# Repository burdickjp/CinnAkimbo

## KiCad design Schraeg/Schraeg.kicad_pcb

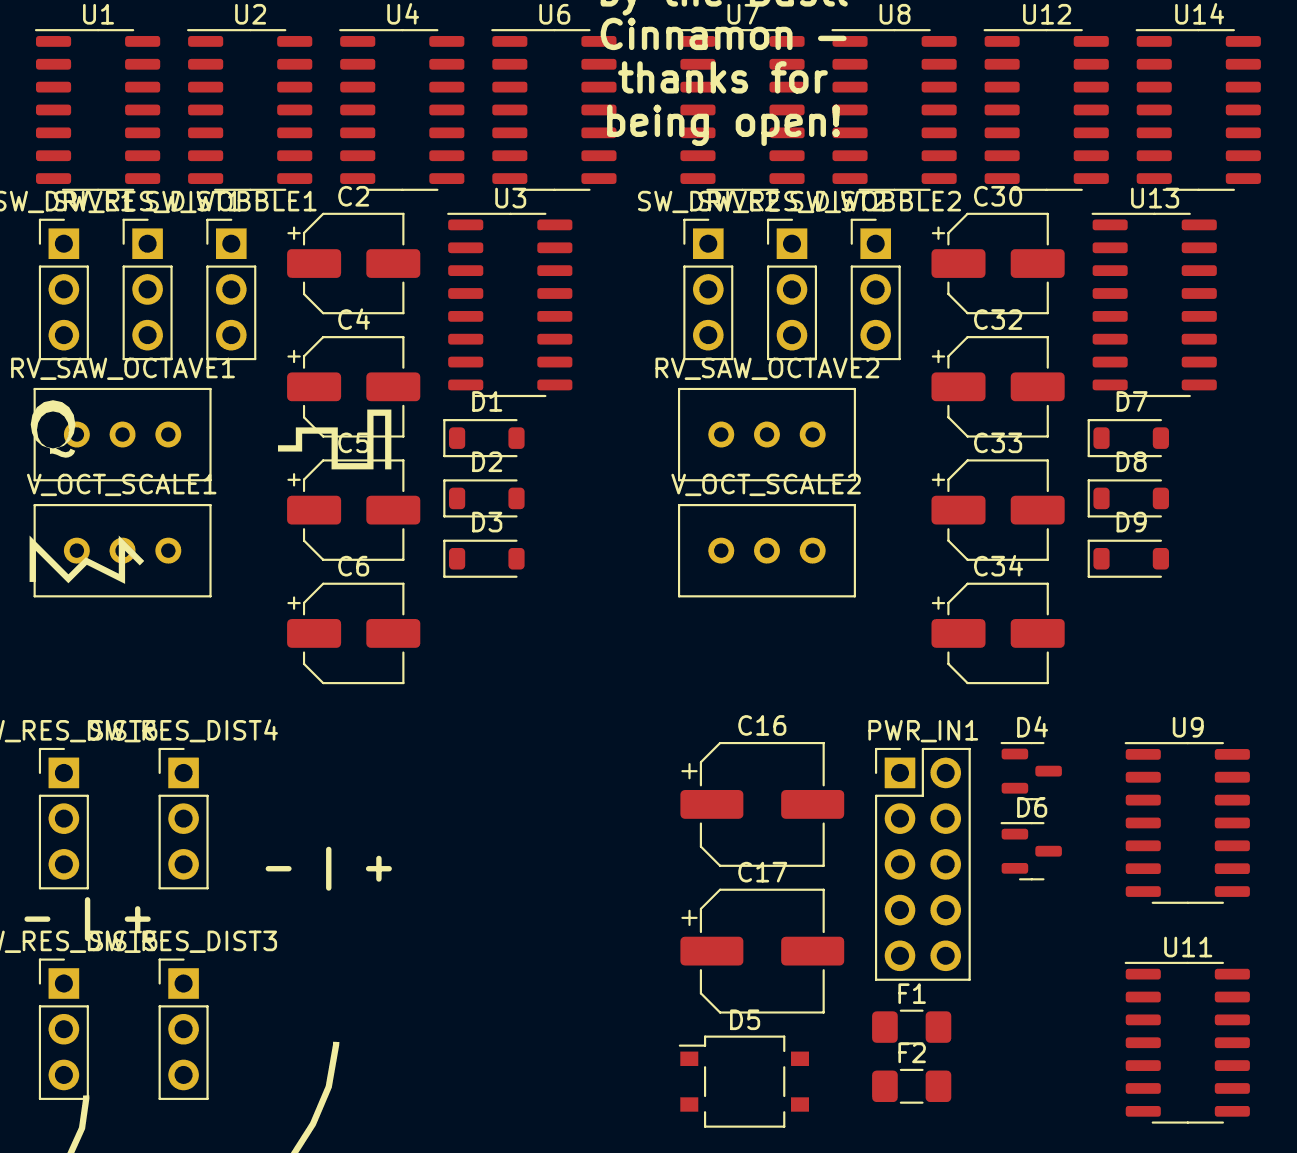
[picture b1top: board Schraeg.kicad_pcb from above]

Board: 2 copper layers, 49 parts (0 on the bottom side), 31 nets, no tracks yet.

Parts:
C2, C4, C5, C6, C30, C32, C33, C34: 10uF; CP_Elec_5x4.5
C16, C17: 22uF; CP_Elec_6.3x5.4
D1, D2, D7, D8: D_Small; D_SOD-123
D3, D9: 5V; D_SOD-123
D4, D6: LM4040DBZ-5; SOT-23
D5: MB2S; TO-269AA
F1, F2: Polyfuse; Fuse_1206_3216Metric_Pad1.42x1.75mm_HandSolder
PWR_IN1: EURO_PWR_2x5; PinHeader_2x05_P2.54mm_Vertical
RV_SAW_OCTAVE1, RV_SAW_OCTAVE2: 100k; Potentiometer_Bourns_3296W_Vertical
SW_DRIVE1, SW_DRIVE2: SW_SPDT; PinHeader_1x03_P2.54mm_Vertical
SW_RES_DIST1, SW_RES_DIST2, SW_RES_DIST3, SW_RES_DIST4, SW_RES_DIST5, SW_RES_DIST6: SW_SPDT; PinHeader_1x03_P2.54mm_Vertical
SW_WOBBLE1, SW_WOBBLE2: SW_SPDT; PinHeader_1x03_P2.54mm_Vertical
U1, U2, U4, U6, U7, U8, U9, U11, U12, U14: TL074; SOIC-14_3.9x8.7mm_P1.27mm
U3, U13: V2164; SOIC-16_3.9x9.9mm_P1.27mm
V_OCT_SCALE1, V_OCT_SCALE2: 5K; Potentiometer_Bourns_3296W_Vertical
svg2mod: G***; Schraeg Panel Graphics Inkscape

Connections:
+12V: C16.1, D5.3 (+), U1.4 (V+), U2.4 (V+), U3.16 (V+), U4.4 (V+), U6.4 (V+), U7.4 (V+), U8.4 (V+), U12.4 (V+), U13.16 (V+), U14.4 (V+)
-12V: C17.2, D5.4 (-), U1.11 (V-), U2.11 (V-), U3.9 (-V), U4.11 (V-), U6.11 (V-), U7.11 (V-), U8.11 (V-), U12.11 (V-), U13.9 (-V), U14.11 (V-)
/Invert Switch A/CV_OUT: SW_RES_DIST3.2 (B), U2.6 (-)
/Invert Switch D/CV_OUT: SW_RES_DIST6.2 (B), U12.6 (-)
/Left Channel/FM_CV_IN: D1.2 (A), U1.9 (-)
/Left Channel/FREQ_CV: D2.1 (K), V_OCT_SCALE1.2, V_OCT_SCALE1.3
/Left Channel/RES_CV: U3.3, U4.1
/Left Channel/RES_MOD: SW_RES_DIST1.3 (C), SW_WOBBLE1.3 (C)
/Right Channel/FM_CV_IN: D7.2 (A), U7.9 (-)
/Right Channel/FREQ_CV: D8.1 (K), V_OCT_SCALE2.2, V_OCT_SCALE2.3
/Right Channel/RES_CV: U13.3, U14.1
/Right Channel/RES_MOD: SW_RES_DIST2.3 (C), SW_WOBBLE2.3 (C)
GND: C16.2, C17.1, D4.2 (A), D6.1 (K), PWR_IN1.3 (GND), PWR_IN1.4 (GND), PWR_IN1.5 (GND), PWR_IN1.6 (GND), PWR_IN1.7 (GND), PWR_IN1.8 (GND), RV_SAW_OCTAVE1.3, RV_SAW_OCTAVE2.3, U1.5 (+), U1.10 (+), U1.12 (+), U2.5 (+), U2.10 (+), U3.8 (GND), U4.3 (+), U4.5 (+), U6.5 (+), U7.5 (+), U7.10 (+), U7.12 (+), U8.5 (+), U9.5 (+), U11.5 (+), U12.5 (+), U12.10 (+), U13.8 (GND), U14.3 (+)
unnamed: D1.1 (K), D2.2 (A), U1.8
unnamed: D3.2 (A), SW_RES_DIST1.2 (B)
unnamed: D5.1, F2.1
unnamed: D5.2, F1.1
unnamed: D7.1 (K), D8.2 (A), U7.8
unnamed: D9.2 (A), SW_RES_DIST2.2 (B)
unnamed: F1.2, PWR_IN1.1 (+12V), PWR_IN1.2 (+12V)
unnamed: F2.2, PWR_IN1.9 (-12V), PWR_IN1.10 (-12V)
unnamed: SW_DRIVE1.2 (B), U1.14
unnamed: SW_DRIVE2.2 (B), U7.14
unnamed: SW_RES_DIST3.1 (A), U4.7
unnamed: SW_RES_DIST4.1 (A), U6.7
unnamed: SW_RES_DIST5.1 (A), U7.7
unnamed: SW_RES_DIST6.1 (A), U8.7
unnamed: RV_SAW_OCTAVE1.1, SW_WOBBLE1.2 (B)
unnamed: RV_SAW_OCTAVE2.1, SW_WOBBLE2.2 (B)
unnamed: U3.4, U4.2 (-)
unnamed: U13.4, U14.2 (-)

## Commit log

2023-09-18 adds schematic PDF
2023-09-18 fixes filter schematic
